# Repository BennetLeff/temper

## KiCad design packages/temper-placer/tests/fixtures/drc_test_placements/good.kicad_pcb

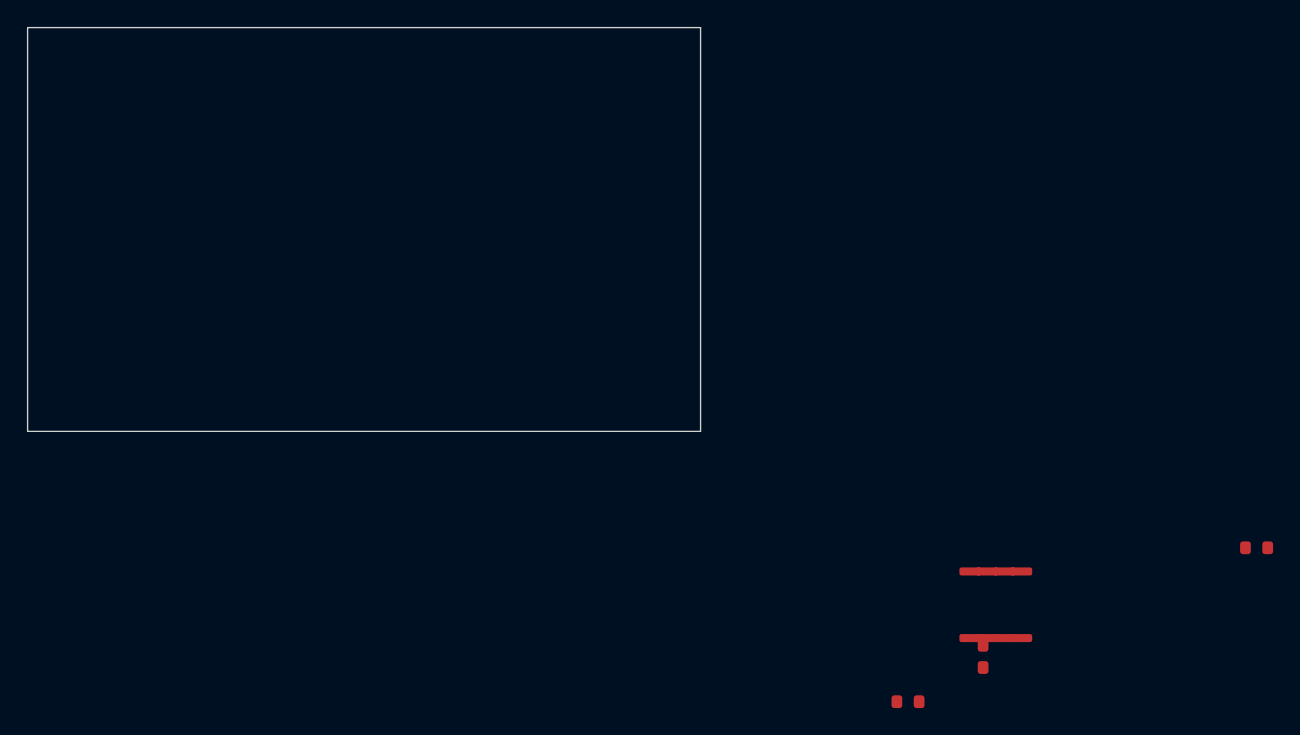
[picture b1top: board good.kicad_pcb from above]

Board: 2 copper layers, 50.0 x 30.0 mm, 4 parts (0 on the bottom side), 4 nets, no tracks yet.

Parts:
C1: 100nF; C_0603_1608Metric
R1: 10k; R_0603_1608Metric
R2: 4.7k; R_0603_1608Metric
U1: LM358; SOIC-8_3.9x4.9mm_P1.27mm

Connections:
GND: C1.2, R2.1, U1.4
SIG1: R1.1, U1.1, U1.5
SIG2: R1.2, R2.2, U1.2, U1.3, U1.6
VCC: C1.1, U1.7, U1.8

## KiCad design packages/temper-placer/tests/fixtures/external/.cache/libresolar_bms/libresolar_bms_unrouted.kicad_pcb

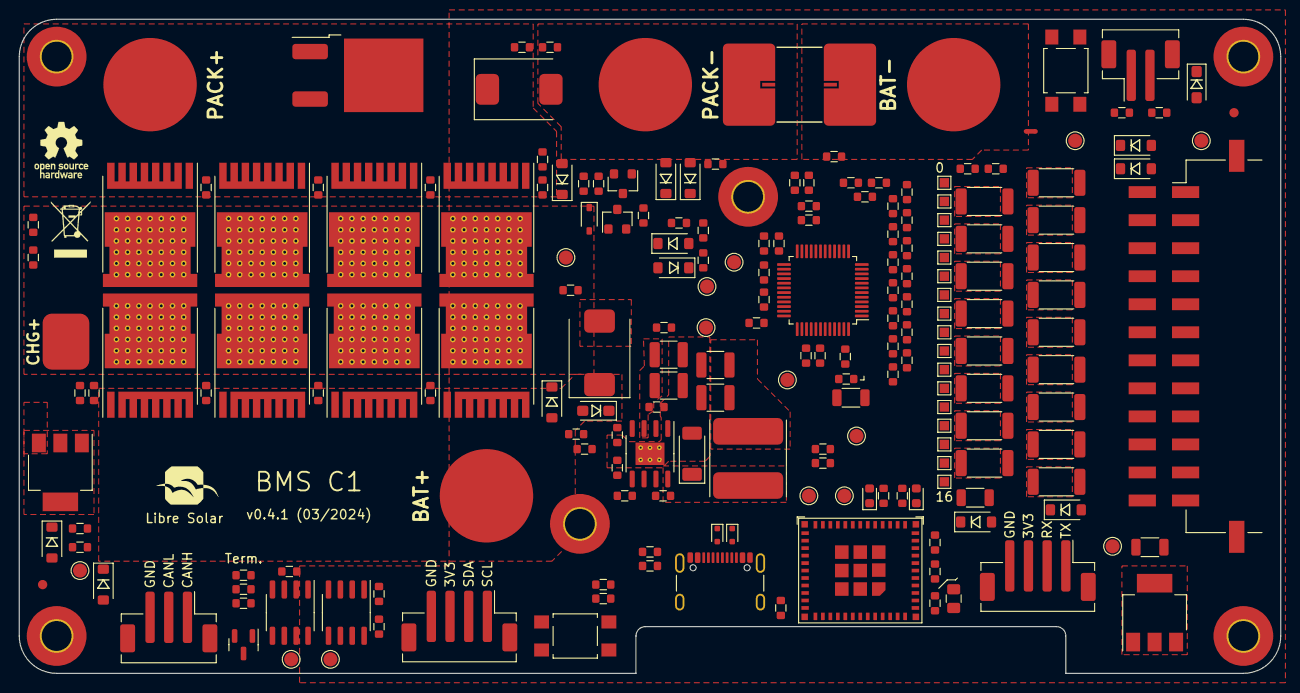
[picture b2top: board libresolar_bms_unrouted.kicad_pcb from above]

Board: 4 copper layers, 135.0 x 70.0 mm, 208 parts (0 on the bottom side), 117 nets, no tracks yet.

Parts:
C1, C2, C3, C4, C5, C6, C7, C8, C9, C10, C11, C12, C13, C14, C15, C16, C26: 220nF; C_0603_1608
C17, C18: 47µF; C_1210_3225
C19, C21, C24, C28, C31, C34, C36, C37, C40, C48, C49, C50, C51, C52: 100nF; C_0603_1608
C20: 2.2µF; C_0603_1608
C22, C23: 2.2µF; C_1210_3225
C25: 1µF; C_1206_3216
C27, C29, C32, C33, C35, C38: 100pF; C_0603_1608
C30, C47: 1µF; C_0603_1608
C46: 10µF; C_0805_2012
D1, D13: PMEG10010ELRX; D_SOD-123F
D2, D5, D10, D15, D16, D20: BAT46W; D_SOD-123
D3, D4: ESD5B5.0ST1G; D_SOD-523
D8: PESD2CANFD; SOT-23
D9: VSS8D3M10-M3/I; D_SOD-128
D11: 3.6V; D_SOD-123
D12: SMCJ70A; D_SMC
D14, D17, D21, D24: 16V; D_SOD-123
D19: 5.1V; D_SOD-323
D22: MURS360; D_SMC
D23: 75V; D_SOD-123
FID1, FID2: Fiducial; Fiducial_1mm_Mask2mm
H1, H2, H3, H4, H5, H6: MountingHole; MountingHole_3.2mm_M3_Pad_TopBottom
J1: MicroFit 2x12; Molex_Micro-Fit_3.0_43045-2410_2x12-1MP_P3.00mm_Horizontal
J2, J6: B4B-PH-SM4; JST_PH_B4B-PH-SM4-TB_1x04-1MP_P2.00mm_Vertical
J3: USB_C_Receptacle_USB2.0; USB_C_Receptacle_GCT_USB4105-xx-A_16P_TopMnt_Horizontal
J4: B3B-PH-SM4; JST_PH_B3B-PH-SM4-TB_1x03-1MP_P2.00mm_Vertical
J5: B2B-PH-SM4; JST_PH_B2B-PH-SM4-TB_1x02-1MP_P2.00mm_Vertical
L2: 22µH; Bourns_SRN8040TA
LED1: LED red; LED_0603_1608Metric
LED2: LED green; LED_0603_1608Metric
LOGO1: OPEN_HARDWARE; OSHW-Logo_5.7x6mm_SilkScreen
LOGO2: LIBRE_SOLAR; LIBRESOLAR_LOGO
NT1: NetTie; NetTie-2_SMD_Pad0.5mm
P1, P2, P3, P4: CONN_01X01; Wuerth_PowerOne_SMD_LF990005
P5: CONN_01X01; SolderWirePad_1x01_SMD_5x10mm
Q1: DMN10H220LE; SOT-223
Q2, Q3, Q4, Q5, Q6, Q7, Q8, Q9: IPT012N08N5; Infineon_PG-HSOF-8-1_ThermalVias
Q10: BSS84; SOT-23
Q11: BSS123N; SOT-23
Q12: ZXMP10A17GTA; SOT-223-3_TabPin2
R1, R2, R3, R4, R5, R6, R7, R8, R9, R10, R11, R12, R13, R14, R15, R16, R17: 20; R_2010_5025
R18: 100; R_1206_3216
R19, R20, R38, R44: 100; R_0603_1608
R21, R37: 0R; R_0603_1608
R22, R23, R46: 1k; R_0603_1608
R24, R26, R62: 1M; R_0603_1608
R25: 10; R_1206_3216
R27, R35, R53, R54: 5.1k; R_0603_1608
R28, R65: 82k; R_0603_1608
R29, R30, R60, R68: 10k; R_0603_1608
R31: 35.7k; R_0603_1608
R32, R33: 2.2k; R_0603_1608
R34: 52.3k; R_0603_1608
R39, R52, R59: 10M; R_0603_1608
R40, R41, R42, R43, R47, R48, R49, R50, R57: 47; R_0603_1608
R45: 300µ; R_Shunt_5931_Kelvin
R51, R61: 68k; R_0603_1608
R56, R64: 62R; R_0603_1608
R58: 470; R_0603_1608
R63: 40; Bourns_PWR163
RT1, RT2: 10k; R_0603_1608
S1, S2: SW_PUSH; SW_SPST_TL3305A
TP1, TP2, TP3, TP4, TP5, TP6, TP7, TP8, TP9, TP10, TP12, TP13, TP14, TP15: TestPoint; TestPoint_Pad_D1.5mm
TP16, TP17, TP18, TP19, TP20, TP21, TP22, TP23, TP24, TP25, TP26, TP27, TP28, TP29, TP30, TP31, TP32: TestPoint; TestPoint_Pad_1.0x1.0mm
U1: SN65HVD230; SOIC-8_3.9x4.9mm_P1.27mm
U2: SN65HVD75; SOIC-8_3.9x4.9mm_P1.27mm
U3: LMR38010; SOIC-8-1EP_3.9x4.9mm_P1.27mm_EP2.4x3.1mm_ThermalVias
U4: BQ76952; TQFP-48_7x7mm_P0.5mm
U5: ESP32-C3-MINI-1

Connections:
+3V3: C17.1, C18.1, C19.1, C21.1, C36.1, C46.1, D13.2 (A), J2.3, J6.3, L2.2, R26.2, R28.1, R32.2, R33.2, R68.2, U1.3 (VCC), U2.8 (VCC), U5.3 (3V3)
/BAT+: C34.1, C49.1, D1.2 (A), D2.1 (K), D12.1 (K), D14.2 (A), J1.12, P1.1, Q2.2 (S), Q3.2 (S), Q4.2 (S), Q5.2 (S), R39.2
/BAT-: C48.2, D12.2 (A), J1.3, NT1.1, P2.1, R45.1
/BQ76952/ALERT: R26.1, TP8.1, U4.25 (ALERT), U5.5 (GPIO2/ADC1_CH2)
/BQ76952/BAT: C25.1, C29.1, C30.2, R18.1, U4.47 (BAT)
/BQ76952/BTN_HIGH: D13.1 (K), J5.1, R54.1, S1.2
/BQ76952/CHG: R38.1, TP4.1, U4.45 (CHG)
/BQ76952/CP1: C30.1, TP1.1, U4.46 (CP1)
/BQ76952/DSG: R44.1, TP6.1, U4.43 (DSG)
/BQ76952/LD: R30.1, U4.41 (LD)
/BQ76952/PACK: R29.1, U4.42 (PACK)
/BQ76952/PDSG: D23.1 (K), R61.1, TP7.1, U4.39 (PDSG)
/BQ76952/SHUNT_N: R20.1, R45.3
/BQ76952/SHUNT_P: R19.1, R45.2
/BQ76952/SRN: C27.2, C28.2, R20.2, U4.20 (SRN)
/BQ76952/SRP: C27.1, C28.1, R19.2, U4.18 (SRP)
/BQ76952/TEMP_SHUNT: C38.1, RT2.2, U4.30 (DFETOFF)
/BQ76952/VC0: C1.2, C26.1, D10.1 (K), D11.1 (K), R1.2, TP16.1, U4.16 (VC0)
/BQ76952/VC1: C1.1, C2.2, R2.2, TP17.1, U4.15 (VC1)
/BQ76952/VC2: C2.1, C3.2, R3.2, TP18.1, U4.14 (VC2)
/BQ76952/VC3: C3.1, C4.2, R4.2, TP19.1, U4.13 (VC3)
/BQ76952/VC4: C4.1, C5.2, R5.2, TP20.1, U4.12 (VC4)
/BQ76952/VC5: C5.1, C6.2, R6.2, TP21.1, U4.11 (VC5)
/BQ76952/VC6: C6.1, C7.2, R7.2, TP22.1, U4.10 (VC6)
/BQ76952/VC7: C7.1, C8.2, R8.2, TP23.1, U4.9 (VC7)
/BQ76952/VC8: C8.1, C9.2, R9.2, TP24.1, U4.8 (VC8)
/BQ76952/VC9: C9.1, C10.2, R10.2, TP25.1, U4.7 (VC9)
/BQ76952/VC10: C10.1, C11.2, R11.2, TP26.1, U4.6 (VC10)
/BQ76952/VC11: C11.1, C12.2, R12.2, TP27.1, U4.5 (VC11)
/BQ76952/VC12: C12.1, C13.2, R13.2, TP28.1, U4.4 (VC12)
/BQ76952/VC13: C13.1, C14.2, R14.2, TP29.1, U4.3 (VC13)
/BQ76952/VC14: C14.1, C15.2, R15.2, TP30.1, U4.2 (VC14)
/BQ76952/VC15: C15.1, C16.2, R16.2, TP31.1, U4.1 (VC15)
/BQ76952/VC16: C16.1, R17.2, TP32.1, U4.48 (VC16)
/BQ76952/WAKE: R54.2, TP15.1, U4.22 (TS2)
/BTN_LOW: C31.2, J5.2, R53.2, S1.1, TP10.1, U5.6 (GPIO3/ADC1_CH3)
/C1+: J1.4, R2.1
/C1-: J1.15, R1.1
/C2+: J1.16, R3.1
/C3+: J1.5, R4.1
/C4+: J1.17, R5.1
/C5+: J1.6, R6.1
/C6+: J1.18, R7.1
/C7+: J1.7, R8.1
/C8+: J1.19, R9.1
/C9+: J1.8, R10.1
/C10+: J1.20, R11.1
/C11+: J1.9, R12.1
/C12+: J1.21, R13.1
/C13+: J1.10, R14.1
/C14+: J1.22, R15.1
/C15+: J1.11, R16.1
/C16+: D2.2 (A), D5.2 (A), J1.23, R17.1
/CAN_H: D8.2 (K), J4.1, R56.1, TP2.1, U1.7 (CANH), U2.6 (A)
/CAN_L: D8.1 (K), J4.2, R64.2, TP3.1, U1.6 (CANL), U2.7 (B)
/CHG+: D24.1 (K), P5.1, Q2.3 (D), Q3.3 (D), Q4.3 (D), Q5.3 (D), Q6.3 (D), Q7.3 (D), Q8.3 (D), Q9.3 (D), Q12.3 (S), R62.1, TP9.1
/ESP32-C3 MCU/CAN_RX: U1.4 (R), U2.1 (R), U5.18 (GPIO4/ADC1_CH4)
/ESP32-C3 MCU/CAN_STB: R21.2, U5.16 (GPIO10)
/ESP32-C3 MCU/CAN_TX: U1.1 (D), U2.4 (D), U5.19 (GPIO5/ADC2_CH0)
/ESP32-C3 MCU/NRST: C47.1, R68.1, S2.2, U5.8 (EN/CHIP_PU)
/ESP32-C3 MCU/RS485_DE: U2.3 (DE), U5.20 (GPIO6)
/ESP32-C3 MCU/RS485_~RE: U2.2 (~RE), U5.21 (GPIO7)
/ESP32-C3 MCU/USB_D+: D4.2 (A2), J3.A6 (D+), J3.B6 (D+), U5.27 (GPIO19/USB_D+)
/ESP32-C3 MCU/USB_D-: D3.2 (A2), J3.A7 (D-), J3.B7 (D-), U5.26 (GPIO18/USB_D-)
/FUSE: J1.24, R25.2, TP14.1
/I2C_SCL: J2.1, R33.1, TP13.1, U4.26 (SCL), U5.23 (GPIO9)
/I2C_SDA: J2.2, R32.1, TP12.1, U4.27 (SDA), U5.22 (GPIO8)
/LED_GREEN: R23.2, U5.12 (GPIO0/ADC1_CH0/XTAL_32K_P)
/LED_RED: R22.2, U5.13 (GPIO1/ADC1_CH1/XTAL_32K_N)
/PACK+: C50.2, C51.1, D17.2 (A), D21.2 (A), D22.1 (K), P3.1, Q6.2 (S), Q7.2 (S), Q8.2 (S), Q9.2 (S), Q11.2 (S), R29.2, R30.2, R52.2, R57.1, R59.2, R63.2, R63.3
/PACK-: C52.2, D22.2 (A), P4.1, R45.4, R60.1
/Power Part/CHG_G: D14.1 (K), R38.2, R39.1, R40.1, R41.1, R42.1, R43.1
/Power Part/DSG_G: D17.1 (K), D19.1 (K), Q10.2 (S), R47.2, R48.2, R49.2, R50.2, R52.1, R58.1
/Power Supply/EN: R37.1, TP5.1, U3.2 (EN)
/Power Supply/FB: R28.2, R31.1, U3.5 (FB)
/Power Supply/SW: C24.2, D9.1 (K), L2.1, U3.8 (SW)
/Power Supply/VIN: C22.1, C23.1, C40.1, D1.1 (K), U3.3 (VIN)
/REG18: C20.1, R37.2, U4.24 (REG18)
/TEMP1: C32.1, J1.13, U4.21 (TS1)
/TEMP2: C33.1, J1.14, U4.23 (TS3)
/TEMP_FETS: C35.1, RT1.2, U4.31 (DCHG)
/UART_RX: J6.2, U5.30 (GPIO20/U0RXD)
/UART_TX: J6.1, U5.31 (GPIO21/U0TXD)
GND: C17.2, C18.2, C19.2, C20.2, C21.2, C22.2, C23.2, C25.2, C26.2, C29.2, C31.1, C32.2, C33.2, C35.2, C36.2, C37.2, C38.2, C40.2, C46.2, C47.2, D3.1 (A1), D4.1 (A1), D8.3 (A), D9.2 (A), D10.2 (A), D11.2 (A), D15.2 (A), D23.2 (A), J1.1, J1.2, J1.MP (MountPin), J2.4, J2.MP (MountPin), J3.A1 (GND), J3.A12 (GND), J3.B1 (GND), J3.B12 (GND), J4.3, J4.MP (MountPin), J5.MP (MountPin), J6.4, J6.MP (MountPin), LED1.1 (K), LED2.1 (K), NT1.2, Q1.3 (S), R24.1, R27.1, R31.2, R34.2, R35.1, R53.1, R65.2, RT1.1, RT2.1, S2.1, U1.2 (GND), U2.5 (GND), U3.1 (GND), U3.9 (PADGND), U4.17 (VSS), U4.33 (RST_SHUT), U4.36 (REGIN), U4.37 (BREG), U5.1 (GND), U5.2 (GND), U5.11 (GND), U5.14 (GND), U5.36 (GND)
unnamed: C34.2, C48.1
unnamed: C37.1, R56.2, R64.1
unnamed: C49.2, C50.1
unnamed: C51.2, C52.1
unnamed: D5.1 (K), R18.2
unnamed: D15.1 (K), R44.2, R46.1
unnamed: D16.2 (A), R46.2, R51.1
unnamed: D16.1 (K), D19.2 (A), Q10.1 (G), R51.2
unnamed: D20.2 (A), R60.2
unnamed: D20.1 (K), D21.1 (K), Q11.1 (G), R59.1
unnamed: D24.2 (A), Q12.1 (G), R61.2, R62.2
unnamed: J3.A5 (CC1), R35.2
unnamed: J3.B5 (CC2), R27.2
unnamed: J3.S1 (SHIELD), R24.2
unnamed: LED1.2 (A), R22.1
unnamed: LED2.2 (A), R23.1
unnamed: Q1.2 (D), Q1.4 (D), R25.1
unnamed: Q1.1 (G), U4.38 (FUSE)
unnamed: Q2.1 (G), R40.2
unnamed: Q3.1 (G), R41.2
unnamed: Q4.1 (G), R42.2
unnamed: Q5.1 (G), R43.2
unnamed: Q6.1 (G), R47.1
unnamed: Q7.1 (G), R48.1
unnamed: Q8.1 (G), R49.1
unnamed: Q9.1 (G), R50.1
unnamed: Q10.3 (D), R57.2
unnamed: Q11.3 (D), R58.2
unnamed: Q12.2 (D), R63.1
unnamed: R21.1, U1.8 (Rs)
unnamed: C24.1, U3.7 (BOOT)
unnamed: R34.1, U3.4 (RT/SYNC)
unnamed: R65.1, U4.34 (REG2), U4.35 (REG1)

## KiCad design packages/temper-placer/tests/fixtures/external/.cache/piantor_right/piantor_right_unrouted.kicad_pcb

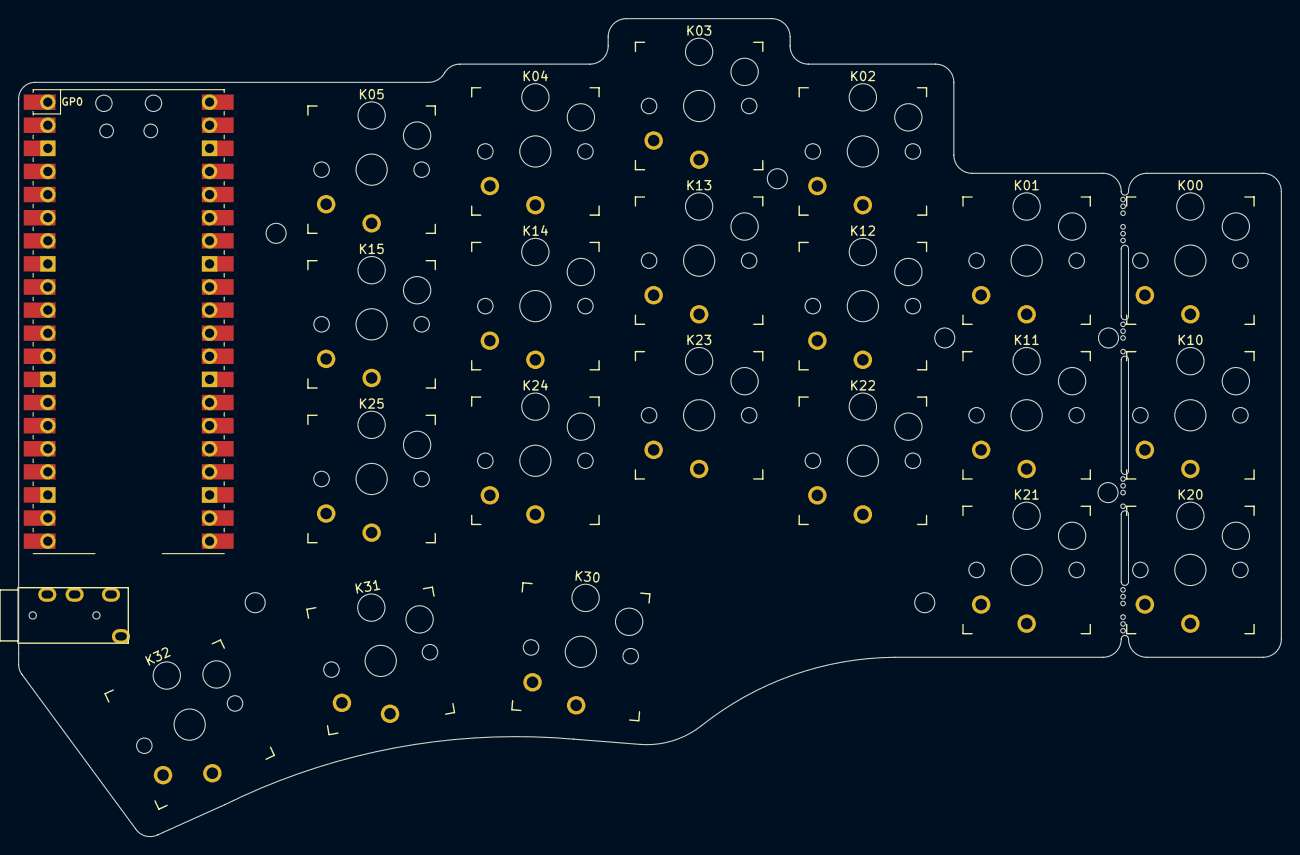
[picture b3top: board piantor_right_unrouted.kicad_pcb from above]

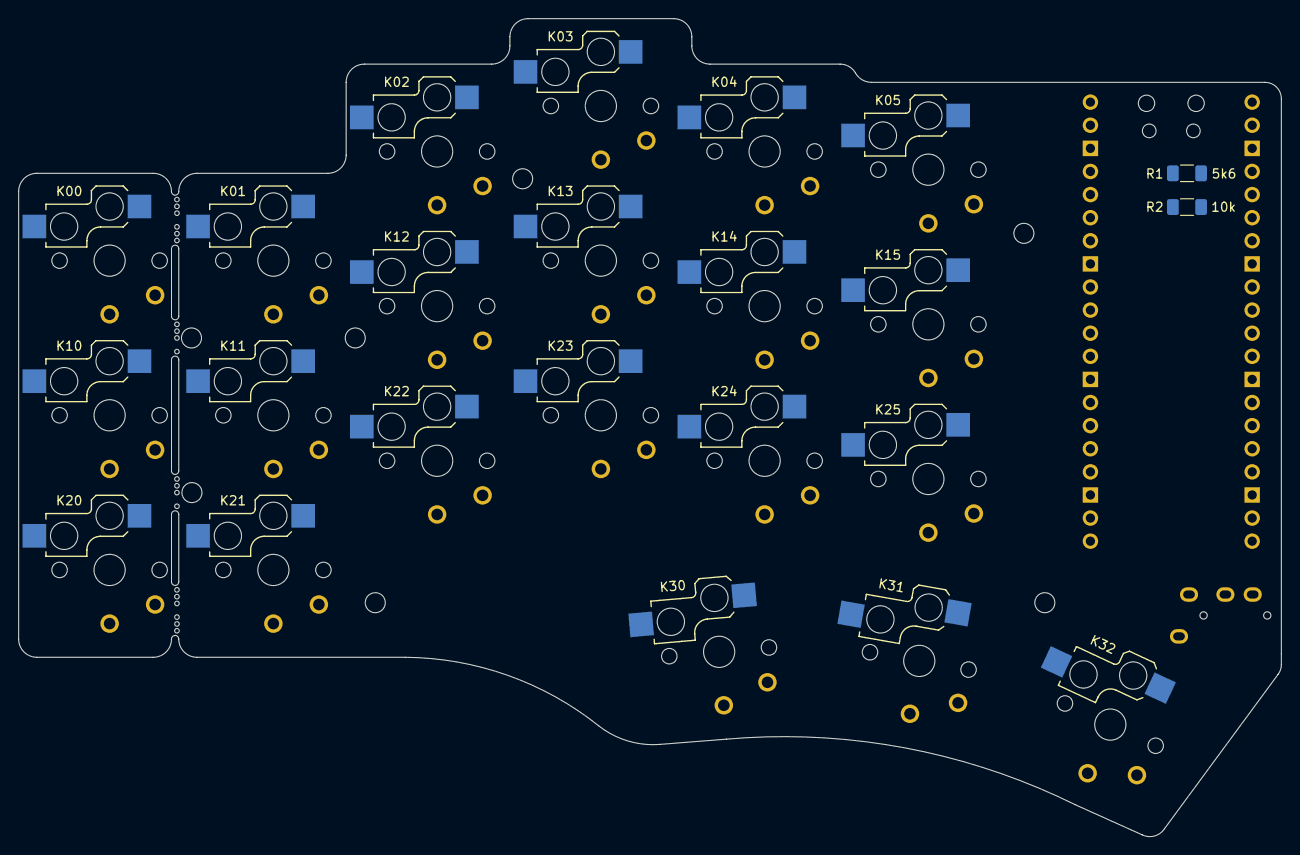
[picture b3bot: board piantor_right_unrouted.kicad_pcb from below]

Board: 2 copper layers, 138.8 x 89.9 mm, 36 parts (13 on the bottom side), 27 nets, no tracks yet.

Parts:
H1, H1#2, H2, H3, H4, H4#2, H4#3: MountingHole; MountingHole_2.2mm_M2-8mm
J1: TRRS; TRRS-PJ-320A
K00, K01, K02, K03, K04, K05, K10, K11, K12, K13, K14, K15, K20, K21, K22, K23, K24, K25, K30, K31, K32: KEYSW; Kailh_socket_PG1350_optional
MB1, MB2: MountingHole; mousebites_2
MB3, MB4: MountingHole; mousebites_3
R1: 5k6; R_1206_3216Metric_Pad1.30x1.75mm_HandSolder
R2: 10k; R_1206_3216Metric_Pad1.30x1.75mm_HandSolder
U2: Pico; RPi_Pico_SMD_TH

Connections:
/k00: K00.1, U2.15 (GPIO11)
/k01: K01.1, U2.11 (GPIO8)
/k02: K02.1, U2.7 (GPIO5)
/k03: K03.1, U2.4 (GPIO2)
/k04: K04.1, U2.27 (GPIO21)
/k05: K05.1, U2.29 (GPIO22)
/k10: K10.1, U2.16 (GPIO12)
/k11: K11.1, U2.12 (GPIO9)
/k12: K12.1, U2.9 (GPIO6)
/k13: K13.1, U2.5 (GPIO3)
/k14: K14.1, U2.25 (GPIO19)
/k15: K15.1, U2.26 (GPIO20)
/k20: K20.1, U2.17 (GPIO13)
/k21: K21.1, U2.14 (GPIO10)
/k22: K22.1, U2.10 (GPIO7)
/k23: K23.1, U2.6 (GPIO4)
/k24: K24.1, U2.22 (GPIO17)
/k25: K25.1, U2.24 (GPIO18)
/k30: K30.1, U2.21 (GPIO16)
/k31: K31.1, U2.19 (GPIO14)
/k32: K32.1, U2.20 (GPIO15)
GND: J1.3 (RING1), K00.2, K01.2, K02.2, K03.2, K04.2, K05.2, K10.2, K11.2, K12.2, K13.2, K14.2, K15.2, K20.2, K21.2, K22.2, K23.2, K24.2, K25.2, K30.2, K31.2, K32.2, R2.2, U2.3 (GND), U2.8 (GND), U2.13 (GND), U2.18 (GND), U2.23 (GND), U2.28 (GND), U2.33 (AGND), U2.38 (GND)
VBUS: R1.1, U2.40 (VBUS)
VCC: J1.2 (TIP), U2.39 (VSYS)
rx: J1.4 (RING2), U2.2 (GPIO1)
tx: J1.1 (SLEEVE), U2.1 (GPIO0)
vbus_sense: R1.2, R2.1, U2.34 (GPIO28_ADC2)

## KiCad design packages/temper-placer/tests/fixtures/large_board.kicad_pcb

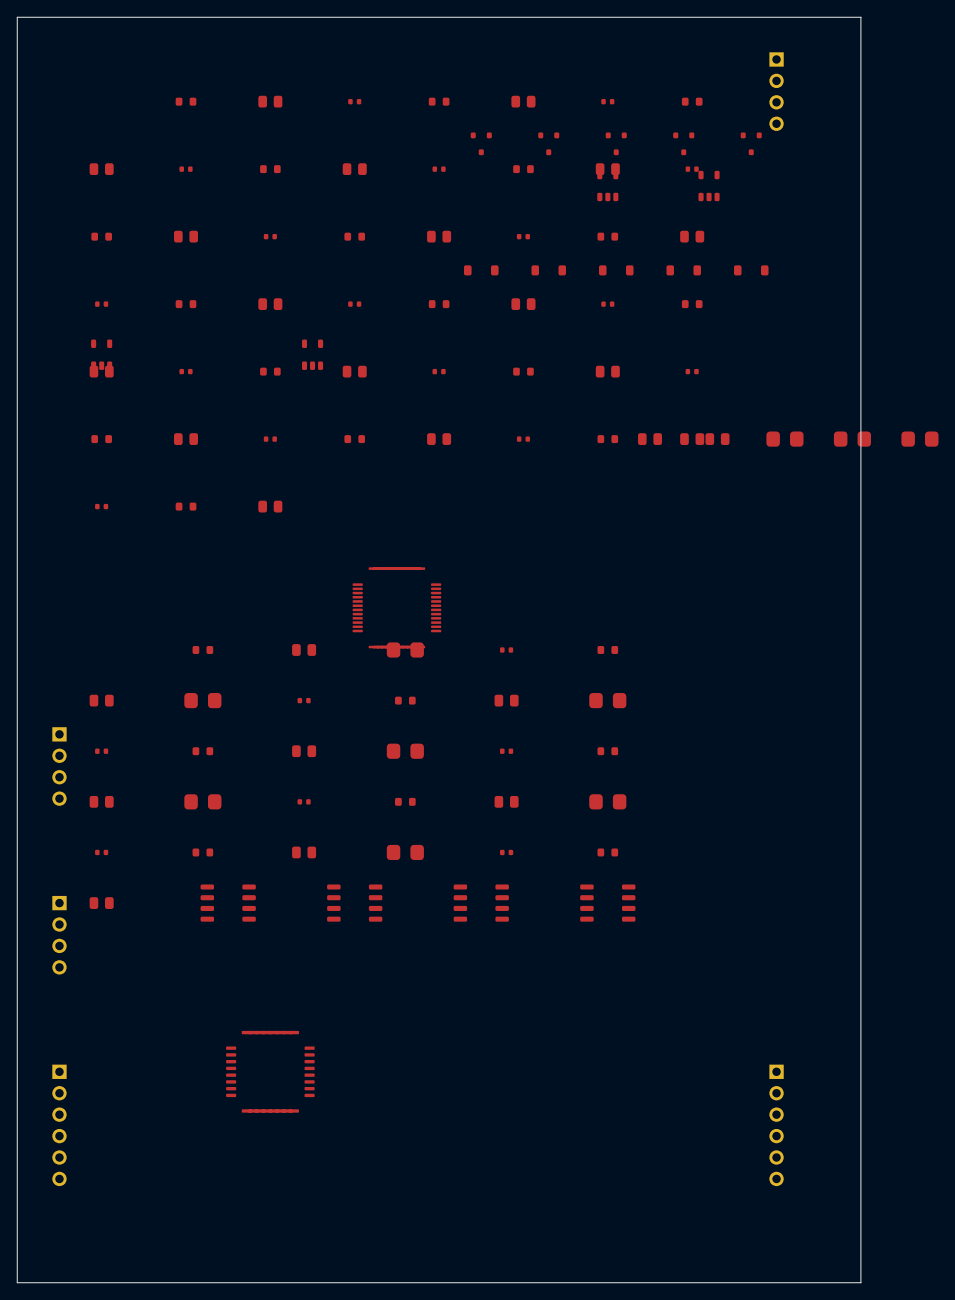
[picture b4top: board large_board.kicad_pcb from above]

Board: 2 copper layers, 100.0 x 150.0 mm, 110 parts (0 on the bottom side), 35 nets, no tracks yet.

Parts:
C1, C13, C25: 1nF; C_0603_1608Metric
C2, C14, C26: 100nF; C_0805_2012Metric
C3, C15, C27: 1uF; C_1206_3216Metric
C4, C16, C28: 10uF; C_0402_1005Metric
C5, C17, C29: 22uF; C_0603_1608Metric
C6, C18, C30: 100pF; C_0805_2012Metric
C7, C19: 1nF; C_1206_3216Metric
C8, C20: 100nF; C_0402_1005Metric
C9, C21: 1uF; C_0603_1608Metric
C10, C22: 10uF; C_0805_2012Metric
C11, C23: 22uF; C_1206_3216Metric
C12, C24: 100pF; C_0402_1005Metric
D1, D2, D3, D4, D5: 1N4148; D_SOD-123
J1: PROG; PinHeader_1x06_P2.54mm_Vertical
J2: DEBUG; PinHeader_1x04_P2.54mm_Vertical
J3: I2C; PinHeader_1x04_P2.54mm_Vertical
J4: PWR_IN; PinHeader_1x04_P2.54mm_Vertical
J5: ANALOG; PinHeader_1x06_P2.54mm_Vertical
L1, L2: 10uH; L_0805_2012Metric
L3, L4, L5: 10uH; L_1206_3216Metric
Q1, Q2, Q3, Q4, Q5: 2N7002; SOT-23
R1, R22, R43: 1k; R_0603_1608Metric
R2, R23, R44: 4.7k; R_0805_2012Metric
R3, R24, R45: 10k; R_0402_1005Metric
R4, R25, R46: 22k; R_0603_1608Metric
R5, R26, R47: 47k; R_0805_2012Metric
R6, R27, R48: 100k; R_0402_1005Metric
R7, R28, R49: 100; R_0603_1608Metric
R8, R29, R50: 1k; R_0805_2012Metric
R9, R30: 4.7k; R_0402_1005Metric
R10, R31: 10k; R_0603_1608Metric
R11, R32: 22k; R_0805_2012Metric
R12, R33: 47k; R_0402_1005Metric
R13, R34: 100k; R_0603_1608Metric
R14, R35: 100; R_0805_2012Metric
R15, R36: 1k; R_0402_1005Metric
R16, R37: 4.7k; R_0603_1608Metric
R17, R38: 10k; R_0805_2012Metric
R18, R39: 22k; R_0402_1005Metric
R19, R40: 47k; R_0603_1608Metric
R20, R41: 100k; R_0805_2012Metric
R21, R42: 100; R_0402_1005Metric
U1: STM32F103; TQFP-48_7x7mm_P0.5mm
U2, U3, U4, U5: LM358; SOIC-8_3.9x4.9mm_P1.27mm
U6, U7: AMS1117; SOT-23-5
U8: MAX31865; TQFP-32_7x7mm_P0.8mm
U9, U10: UCC27511; SOT-23-5

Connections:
AN1: J5.1, R8.2, R24.1, R48.2, U1.18, U2.1
AN2: J5.2, R9.1, R33.2, R49.1, U1.19, U2.2, U3.1
AN3: J5.3, R18.2, R34.1, U1.20, U3.2, U4.1
AN4: J5.4, R3.2, R19.1, R43.2, U1.21, U4.2, U5.1
AN5: R4.1, R28.2, R44.1, U1.22, U5.2
AN6: R13.2, R29.1, U1.23
AN7: R14.1, R38.2, U1.24
AN8: R23.2, R39.1, U1.25
GND: C1.2, C2.2, C3.2, C4.2, C5.2, C6.2, C7.2, C8.2, C9.2, C10.2, C11.2, C12.2, C13.2, C14.2, C15.2, C16.2, C17.2, C18.2, C19.2, C20.2, C21.2, C22.2, C23.2, C24.2, C25.2, C26.2, C27.2, C28.2, C29.2, C30.2, D1.2, D2.2, D3.2, D4.2, D5.2, J1.2, J2.2, J3.2, J4.2, J4.3, J5.5, Q1.2, Q2.2, Q3.2, Q4.2, Q5.2, R2.1, R5.2, R7.1, R10.2, R12.1, R15.2, R17.1, R20.2, R22.1, R25.2, R27.1, R30.2, R32.1, R35.2, R37.1, R40.2, R42.1, R45.2, R47.1, R50.2, U1.1, U1.26, U1.28, U1.30, U2.3, U2.4, U3.3, U3.4, U4.3, U4.4, U5.3, U5.4, U6.2, U6.3, U7.2, U7.3, U8.2, U8.8, U8.10, U8.16, U8.18, U8.24, U8.26, U8.32, U9.5, U10.5
HV_DC: C3.1, C7.1, C11.1, C15.1, C19.1, C23.1, C27.1, D5.1, L4.1
I2C_SCL: J3.4, U1.11
I2C_SDA: J3.3, U1.10
MCU_RST: J1.6, U1.3
PWM1: Q1.3, U1.14, U9.4
PWM2: Q2.3, U1.15, U10.4
PWM3: Q3.3, U1.16
PWM4: Q4.3, Q5.3, U1.17
SIG1: Q1.1, U1.32, U2.5
SIG2: Q2.1, R1.2, R11.2, R21.2, R31.2, R41.2, U1.33, U2.6, U3.5
SIG3: Q3.1, U1.34, U3.6, U4.5
SIG4: Q4.1, R3.1, R13.1, R23.1, R33.1, R43.1, U1.35, U4.6, U5.5
SIG5: Q5.1, U1.36, U5.6
SIG7: R6.2, R16.2, R26.2, R36.2, R46.2, U1.38
SIG9: R8.1, R18.1, R28.1, R38.1, R48.1
SPI_CLK: J1.5, U1.7, U8.5, U8.13, U8.21, U8.29
SPI_MISO: J1.4, U1.6, U8.4, U8.12, U8.20, U8.28
SPI_MOSI: J1.3, U1.5, U8.3, U8.11, U8.19, U8.27
TEMP_CS: U8.6, U8.14, U8.22, U8.30
TEMP_OUT: U8.7, U8.15, U8.23, U8.31
UART_RX: J2.4, U1.13
UART_TX: J2.3, U1.12
VCC: C4.1, C8.1, C12.1, C16.1, C20.1, C24.1, C28.1, D1.1, J4.1, J4.4, L1.1, L2.2, L3.2, R4.2, R5.1, R9.2, R10.1, R14.2, R15.1, R19.2, R20.1, R24.2, R25.1, R29.2, R30.1, R34.2, R35.1, R39.2, R40.1, R44.2, R45.1, R49.2, R50.1, U2.7, U2.8, U3.7, U3.8, U4.7, U4.8, U5.7, U5.8, U6.1, U7.1
VCC_3V3: C1.1, C5.1, C9.1, C13.1, C17.1, C21.1, C25.1, C29.1, D2.1, J1.1, J2.1, J3.1, J5.6, L2.1, R1.1, R2.2, R6.1, R7.2, R11.1, R12.2, R16.1, R17.2, R21.1, R22.2, R26.1, R27.2, R31.1, R32.2, R36.1, R37.2, R41.1, R42.2, R46.1, R47.2, U1.2, U1.27, U1.29, U1.31, U6.4, U6.5, U7.4, U7.5, U8.1, U8.9, U8.17, U8.25
VCC_5V: C2.1, C6.1, C10.1, C14.1, C18.1, C22.1, C26.1, C30.1, D3.1, L1.2, L3.1
VCC_15V: D4.1, L4.2, U9.1, U10.1

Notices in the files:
packages/temper-placer/tests/fixtures/external/.cache/libresolar_bms/libresolar_bms_unrouted.kicad_pcb:
License: CERN-OHL-W
